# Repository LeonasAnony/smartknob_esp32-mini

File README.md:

# SmartKnob

SmartKnob is an open-source input device with software-configurable endstops and virtual detents. Original by [Scott Bezek](https://github.com/scottbez1/smartknob).

A brushless gimbal motor is paired with a magnetic encoder to provide closed-loop torque feedback control, making it
possible to dynamically create and adjust the feel of detents and endstops.

# Modifications
- ESP32-S3-MINI-1N8
- 24x WS2812 20x20 LED
- SMD Resistor 4 direction Force Sensor
- Accelerometer

# Handheld Version
Handheld Mod in branch [handheld](https://github.com/LeonasAnony/smartknob_esp32-mini/tree/handheld)

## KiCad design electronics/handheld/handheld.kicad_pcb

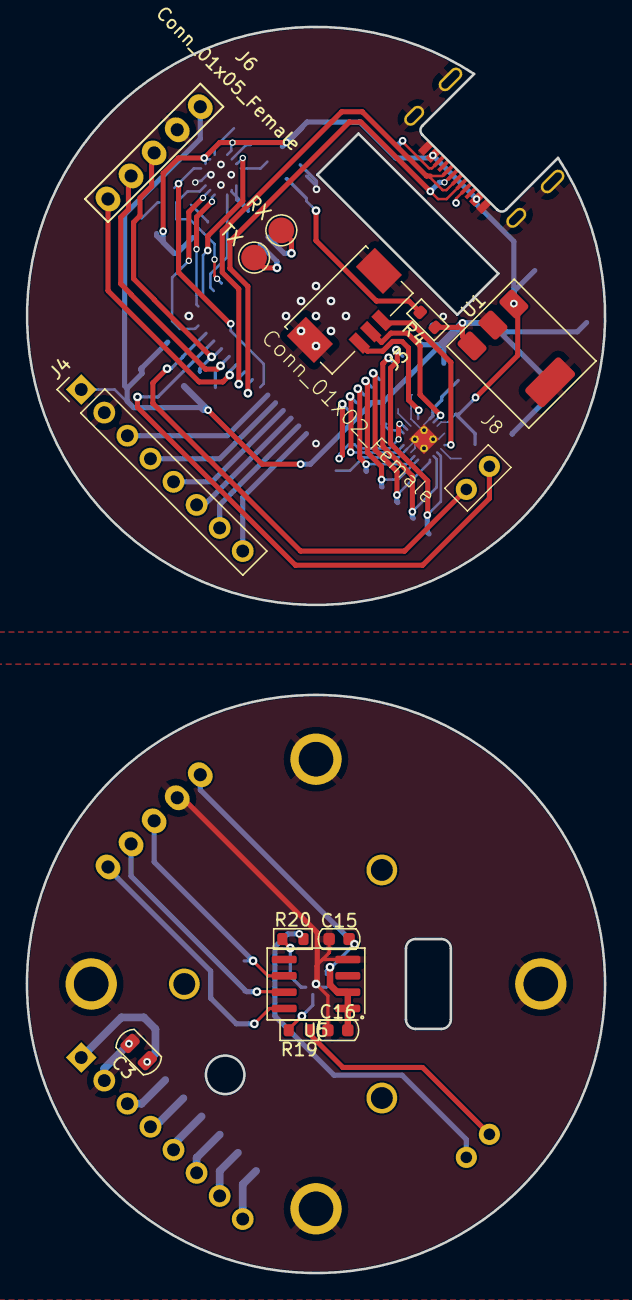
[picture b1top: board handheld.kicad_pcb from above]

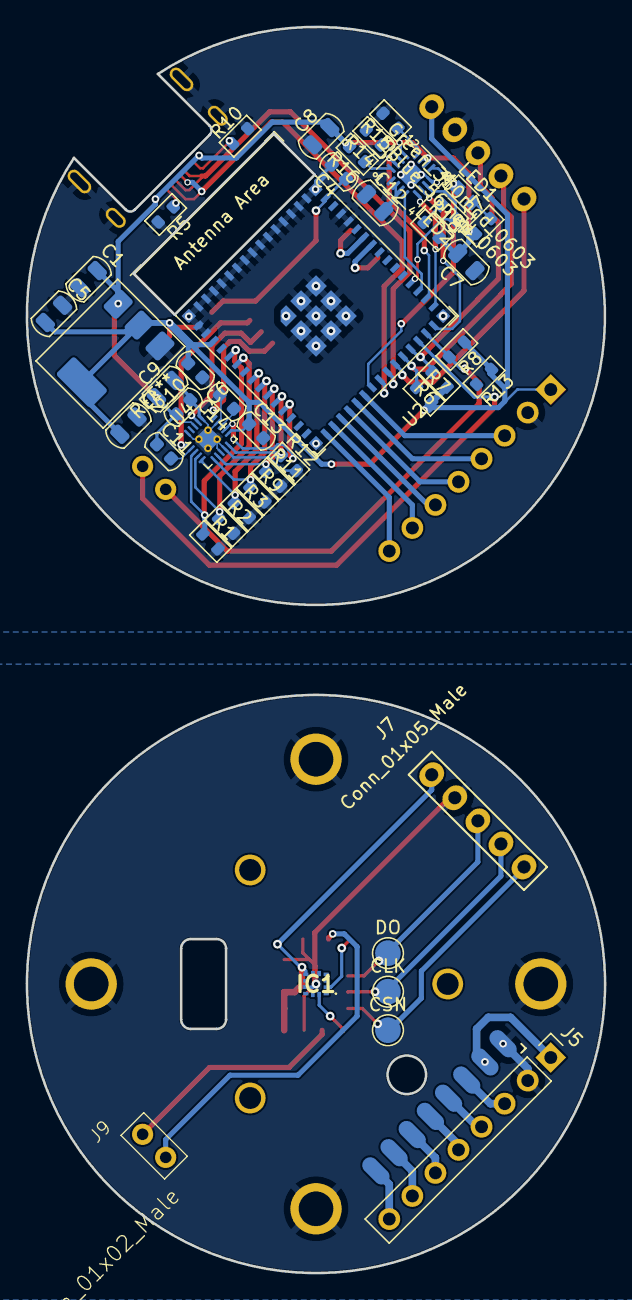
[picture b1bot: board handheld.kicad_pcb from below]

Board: 2 copper layers, 45.0 x 97.0 mm, 66 parts (43 on the bottom side), 60 nets.

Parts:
C1, C2, C3, C5: 10uF; C_0805_2012Metric
C4, C15: 1uF; C_0603_1608Metric
C6, C10, C11, C13, C14, C16: 0.1uF; C_0603_1608Metric
C7: 1uF; C_0805_2012Metric
C8, C12: 4.7uF; C_0805_2012Metric
C9: 22uF; C_0805_2012Metric
H1, H2, H3: MotorHole; MountingHole_M1.6
H4, H5, H6, H7: MountHole; MountingHole_2.7mm_M2.5_Pad
IC1: MXC6655XA
J1: LCD; SolderPads_2mm_8
J2: USB_C_Receptacle_USB2.0; USB4510_NoPaste
J3: BLDC; 532610371
J4: Conn_01x08_Female; Pins_1x08_2.54mm_TH
J5: Conn_01x08_Male; Pins_1x08_2.54mm_TH
J6: Conn_01x05_Female; Pins_1x05_2.54mm_TH
J7: Conn_01x05_Male; Pins_1x05_2.54mm_TH
J8: Conn_01x02_Female; Pins_1x02_2.54mm_TH
J9: Conn_01x02_Male; Pins_1x02_2.54mm_TH
LED1: Blue_56mcd_0603; LED_0603_1608Metric
LED2: Green_350mcd_0603; LED_0603_1608Metric
R1, R2, R3, R4, R9, R11, R12: 10k; R_0603_1608Metric
R5, R10: 5.1k; R_0603_1608Metric
R6, R7, R8, R13: 2.2k; R_0603_1608Metric
R14: 15k; R_0603_1608Metric
R15: 1.18k; R_0603_1608Metric
R16: 1.13k; R_0603_1608Metric
R17, R18: 1.5k; R_0603_1608Metric
R19, R20: 2.7k; R_0603_1608Metric
TP3: TX; TestPoint_Pad_D2.0mm_ValueSilk
TP4: RX; TestPoint_Pad_D2.0mm_ValueSilk
TP11: CSN; TestPoint_Pad_D2.0mm_ValueSilk
TP12: CLK; TestPoint_Pad_D2.0mm_ValueSilk
TP13: DO; TestPoint_Pad_D2.0mm_ValueSilk
U1: AP2114HA-3.3; SOT-223-3_TabPin2
U2: ESP32-S3-MINI-1
U3: BQ24072RGT; VQFN-16-1EP_3x3mm_P0.5mm_EP1.6x1.6mm
U4: TMC6300; QFN-20-1EP_3x3mm_P0.4mm_EP1.65x1.65mm_ThermalVias_LargerVia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
U5: MT6701-CT; SOIC-8_3.9x4.9mm_P1.27mm
Z6: dummy_keepouts; ViewKeepouts3d

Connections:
+3V3: C2.1, C5.1, C6.1, C13.1, J4.1, J6.1, R4.1, R6.1, R7.2, R8.1, R13.1, U1.3 (VO), U2.3 (3V3), U4.11 (VIO/~STDBY)
+5V: C1.1, C7.2, C8.2, C9.1, C10.1, C11.1, J2.A4 (VBUS), J2.A9 (VBUS), J2.B4 (VBUS), J2.B9 (VBUS), R16.2, R17.1, R18.2, U1.1 (VI), U3.10 (OUT), U3.11 (OUT), U3.13 (IN), U4.18 (VS)
/BAT: C12.2, U3.2 (BAT), U3.3 (BAT)
/CE: U2.33 (SPIDQS/GPIO37/FSPIQ/SUBSPIQ), U3.4 (~CE)
/CHG: LED1.1 (C), U2.22 (GPIO18/U1RXD/ADC2_CH7/CLK_OUT3), U3.9 (~CHG)
/EN1: U2.30 (GPIO48/SPICLK_N/SUBSPICLK_N_DIFF), U3.6 (EN1)
/EN2: U2.31 (SPIIO6/GPIO35/FSPID/SUBSPID), U3.5 (EN2)
/ESP32_EN: C4.1, R4.2, U2.45 (EN)
/PGOOD: LED2.1 (C), U2.34 (GPIO38/FSPIWP/SUBSPIWP), U3.7 (~PGOOD)
/TD: U2.32 (SPIIO7/GPIO36/FSPICLK/SUBSPICLK), U3.15 (TD)
/TMC_DIAG: U2.12 (GPIO8/TOUCH8/ADC1_CH7/SUBSPICS1), U4.12 (DIAG)
/TMC_UH: R1.1, U2.5 (GPIO1/TOUCH1/ADC1_CH0), U4.3 (UH)
/TMC_UL: R9.1, U2.9 (GPIO5/TOUCH5/ADC1_CH4), U4.6 (UL)
/TMC_VH: R2.1, U2.6 (GPIO2/TOUCH2/ADC1_CH1), U4.4 (VH)
/TMC_VL: R12.1, U2.11 (GPIO7/TOUCH7/ADC1_CH6), U4.10 (VL)
/TMC_WH: R3.1, U2.8 (GPIO4/TOUCH4/ADC1_CH3), U4.5 (WH)
/TMC_WL: R11.1, U2.10 (GPIO6/TOUCH6/ADC1_CH5), U4.7 (WL)
/USB_CC1: J2.A5 (CC1), R5.1
/USB_CC2: J2.B5 (CC2), R10.1
/USB_D+: J2.A6 (D+), J2.B6 (D+), U2.24 (GPIO20/U1CTS/ADC2_CH9/CLK_OUT1/USB_D+)
/USB_D-: J2.A7 (D-), J2.B7 (D-), U2.23 (GPIO19/U1RTS/ADC2_CH8/CLK_OUT2/USB_D-)
GND: C1.2, C2.2, C3.2, C4.2, C5.2, C6.2, C7.1, C8.1, C9.2, C10.2, C12.1, C13.2, C14.2, C15.1, C16.1, H4.1, H5.1, H6.1, H7.1, IC1.9 (GND), J1.1, J2.A1 (GND), J2.A12 (GND), J2.B1 (GND), J2.B12 (GND), J2.S1 (SHIELD), J4.2, J5.2, J6.2, J7.2, R1.2, R2.2, R3.2, R5.2, R9.2, R10.2, R11.2, R12.2, R14.2, R15.2, U1.2 (GND), U2.1 (GND), U2.2 (GND), U2.42 (GND), U2.43 (GND), U2.46 (GND), U3.8 (VSS), U3.17 (VSS), U4.8 (GND), U4.9 (GND), U4.14 (GND), U4.16 (BRUV), U4.20 (BRW), U4.PAD, U5.4 (GND)
unnamed: C3.1, J1.2, J5.1
unnamed: C11.2, U4.2 (VCP)
unnamed: C14.1, U4.13 (1V8OUT)
unnamed: C15.2, C16.2, IC1.7 (VDD), J7.1, U5.1 (VDD), U5.2 (MODE)
unnamed: IC1.2 (SDA), R20.1
unnamed: IC1.12 (SCL), R19.2
unnamed: J1.3, J5.3
unnamed: J1.4, J5.4
unnamed: J1.5, J5.5
unnamed: J1.6, J5.6
unnamed: J1.7, J5.7
unnamed: J1.8, J5.8
unnamed: J3.1, U4.1 (W)
unnamed: J3.2, U4.17 (V)
unnamed: J3.3, U4.15 (U)
unnamed: J4.3, U2.21 (GPIO17/U1TXD/ADC2_CH6)
unnamed: J4.4, U2.20 (GPIO16/U0CTS/ADC2_CH5/XTAL_32K_NH5)
unnamed: J4.5, U2.19 (GPIO15/U0RTS/ADC2_CH4/XTAL_32K_P)
unnamed: J4.6, U2.18 (GPIO14/TOUCH14/ADC2_CH3/FSPIWP/FSPIDQS/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)
unnamed: J4.7, U2.17 (GPIO13/TOUCH13/ADC2_CH2/FSPIQ/FSPIIO7/S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)
unnamed: J4.8, U2.16 (GPIO12/TOUCH11/ADC2_CH0/FSPICS0/FSPIIO4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)
unnamed: J6.3, U2.27 (GPIO47/SPICLK_P/SUBSPICLK_P_DIFF)
unnamed: J6.4, U2.26 (GPIO26)
unnamed: J6.5, U2.25 (GPIO21)
unnamed: J7.3, TP13.1, U5.6 (A/U/SDA/DO)
unnamed: J7.4, TP12.1, U5.7 (B/V/SCL/CLK)
unnamed: J7.5, TP11.1, U5.8 (Z/W/CSN)
unnamed: J8.1, U2.28 (SPIIO4/GPIO33/FSPIHD/SUBSPIHD)
unnamed: J8.2, U2.29 (SPIIO5/GPIO34/FSPICS0/SUBSPICS0)
unnamed: J9.1, R19.1
unnamed: J9.2, R20.2
unnamed: LED1.2 (A), R17.2
unnamed: LED2.2 (A), R18.1
unnamed: R14.1, U3.14 (TMR)
unnamed: R15.1, U3.12 (ILIM)
unnamed: R16.1, U3.16 (ISET)
unnamed: TP3.1, U2.39 (U0TXD/GPIO43/CLK_OUT1)
unnamed: TP4.1, U2.40 (U0RXD/GPIO44/CLK_OUT2)

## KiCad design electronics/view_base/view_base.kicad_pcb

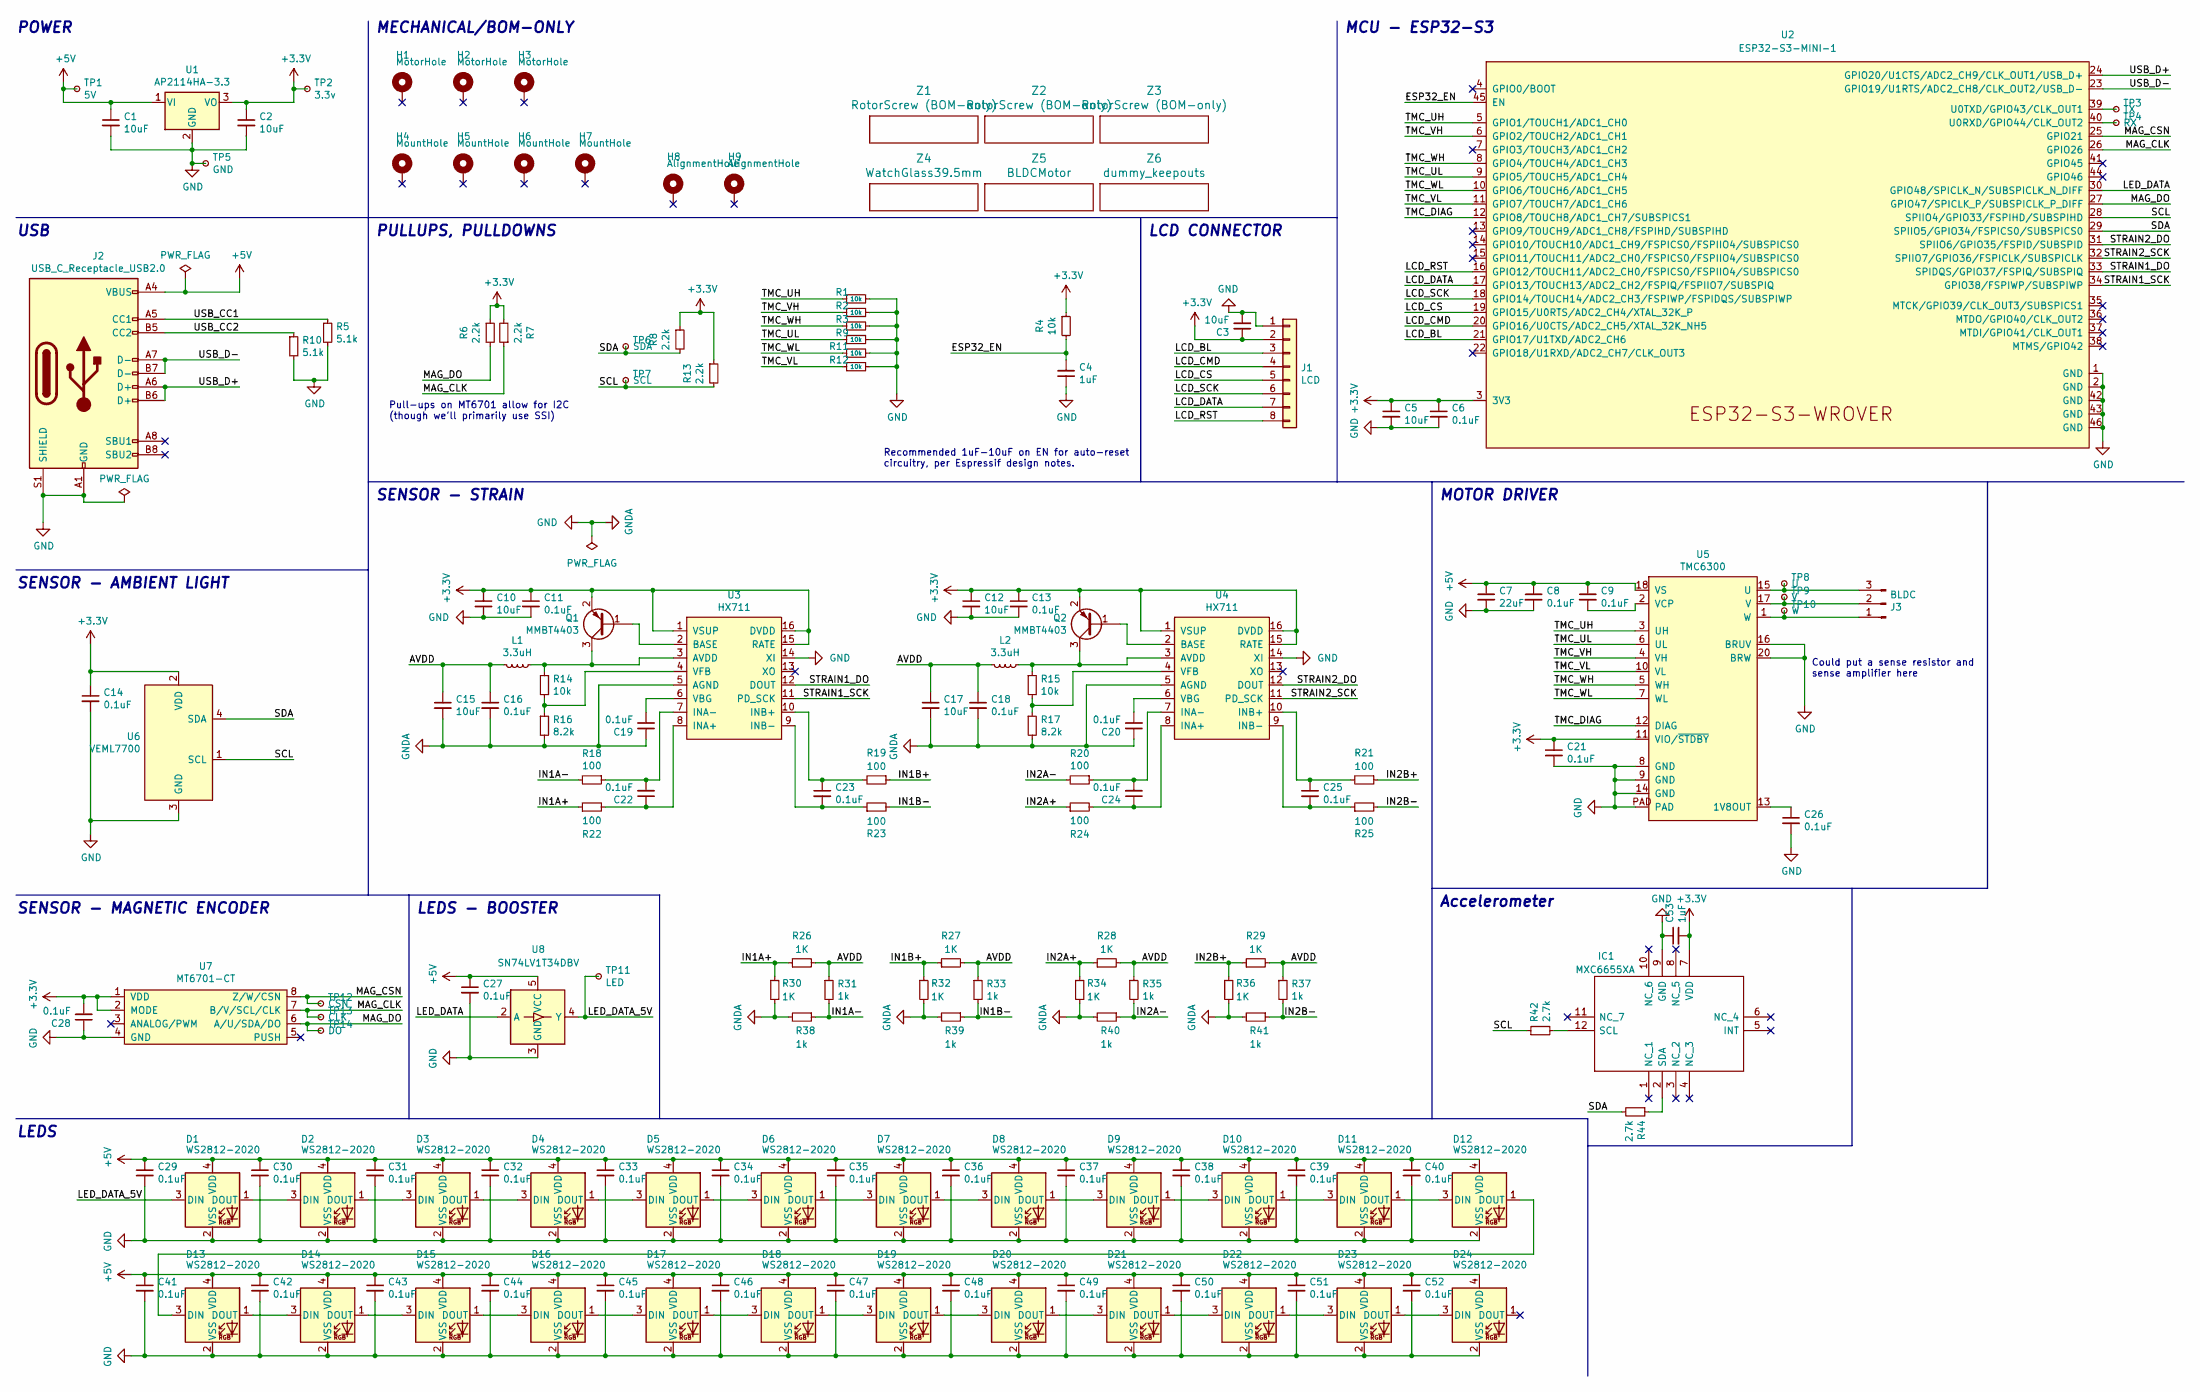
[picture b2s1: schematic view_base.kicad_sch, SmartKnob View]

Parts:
C1, C2, C3, C5, C10, C12, C15, C17: 10uF; C_0805_2012Metric; LCSC C2922480
C4: 1uF; C_0603_1608Metric; Mouser 187-CL10A105KA8NNNC
C6, C8, C9, C11, C13, C14, C16, C18, C19, C20, C21, C22, C23, C24, C25, C26, C27, C28, C29, C30, C31, C32, C33, C34, C35, C36, C37, C38, C39, C40, C41, C42, C43, C44, C45, C46, C47, C48, C49, C50, C51, C52: 0.1uF; C_0603_1608Metric; LCSC C1591
C7: 22uF; C_0805_2012Metric; LCSC C98190
C53: 1uF; C_0603_1608Metric; LCSC C1591
D1, D2, D3, D4, D5, D6, D7, D8, D9, D10, D11, D12, D13, D14, D15, D16, D17, D18, D19, D20, D21, D22, D23, D24: WS2812-2020; Digikey 1528-4691-ND
H1, H2, H3: MotorHole; MountingHole_M1.6
H4, H5, H6, H7: MountHole; MountingHole_2.2mm_M2_ISO7380_Pad_NonVirtual
H8, H9: AlignmentHole; MountingHole_2.2mm_M2_ISO7380_Pad_NonVirtual
IC1: MXC6655XA; Mouser Part Number 438-MXC6655XA
J1: LCD; SolderPads_2mm_8
J2: USB_C_Receptacle_USB2.0; USB4510_NoPaste; LCSC C428463
J3: BLDC; 532610371; LCSC C293630
L1, L2: 3.3uH; L_0805_2012Metric; LCSC C307744
Q1, Q2: MMBT4403; SOT-23; LCSC C78864
R1, R2, R3, R4, R9, R11, R12, R14, R15: 10k; R_0603_1608Metric; LCSC C98220
R5, R10: 5.1k; R_0603_1608Metric; LCSC C105580
R6, R7, R8, R13: 2.2k; R_0603_1608Metric; LCSC C4190
R16, R17: 8.2k; R_0603_1608Metric; LCSC C114637
R18, R19, R20, R21, R22, R23, R24, R25: 100; R_0603_1608Metric; LCSC C319953
R26, R27, R28, R29, R30, R32, R34, R36: 1K; R_2512_6332Metric
R31, R33, R35, R37, R38, R39, R40, R41: 1k; R_0603_1608Metric; LCSC C98220
R42, R44: 2.7k; R_0603_1608Metric; LCSC C98220
TP1: 5V; TestPoint_Pad_D2.0mm_ValueSilk
TP2: 3.3v; TestPoint_Pad_D2.0mm_ValueSilk
TP3: TX; TestPoint_Pad_D2.0mm_ValueSilk
TP4: RX; TestPoint_Pad_D2.0mm_ValueSilk
TP5: GND; TestPoint_Pad_D2.0mm_ValueSilk
TP6: SDA; TestPoint_Pad_D2.0mm_ValueSilk
TP7: SCL; TestPoint_Pad_D2.0mm_ValueSilk
TP8: U; TestPoint_Pad_D2.0mm_ValueSilk
TP9: V; TestPoint_Pad_D2.0mm_ValueSilk
TP10: W; TestPoint_Pad_D2.0mm_ValueSilk
TP11: LED; TestPoint_Pad_D2.0mm_ValueSilk
TP12: CSN; TestPoint_Pad_D2.0mm_ValueSilk
TP13: CLK; TestPoint_Pad_D2.0mm_ValueSilk
TP14: DO; TestPoint_Pad_D2.0mm_ValueSilk
U1: AP2114HA-3.3; SOT-223-3_TabPin2; LCSC C460314
U2: ESP32-S3-MINI-1
U3, U4: HX711; SOIC-16_3.9x9.9mm_P1.27mm; LCSC C43656
U5: TMC6300; QFN-20-1EP_3x3mm_P0.4mm_EP1.65x1.65mm_ThermalVias_LargerVia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; Digikey TMC6300-LA-T
U6: VEML7700; VEML7700-TOP; Digikey VEML7700-TT
U7: MT6701-CT; SOIC-8_3.9x4.9mm_P1.27mm; LCSC C2856764
U8: SN74LV1T34DBV; SOT-23-5; LCSC C100024
Z1, Z2, Z3: RotorScrew (BOM-only); bom_only_no_pin
Z4: WatchGlass39.5mm; bom_only_no_pin
Z5: BLDCMotor; bom_only_no_pin
Z6: dummy_keepouts; ViewKeepouts3d

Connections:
+3V3: C2.1, C3.1, C5.1, C6.1, C10.1, C11.1, C12.1, C13.1, C14.1, C21.1, C28.2, C53.2, IC1.7 (VDD), J1.2, Q1.2 (E), Q2.2 (E), R4.1, R6.1, R7.2, R8.1, R13.1, TP2.1, U1.3 (VO), U2.3 (3V3), U3.1 (VSUP), U3.15 (RATE), U3.16 (DVDD), U4.1 (VSUP), U4.15 (RATE), U4.16 (DVDD), U5.11 (VIO/~STDBY), U6.2 (VDD), U7.1 (VDD), U7.2 (MODE)
+5V: C1.1, C7.1, C8.1, C9.1, C27.1, C29.1, C30.1, C31.1, C32.1, C33.1, C34.1, C35.1, C36.1, C37.1, C38.1, C39.1, C40.1, C41.1, C42.1, C43.1, C44.1, C45.1, C46.1, C47.1, C48.1, C49.1, C50.1, C51.1, C52.1, D1.4 (VDD), D2.4 (VDD), D3.4 (VDD), D4.4 (VDD), D5.4 (VDD), D6.4 (VDD), D7.4 (VDD), D8.4 (VDD), D9.4 (VDD), D10.4 (VDD), D11.4 (VDD), D12.4 (VDD), D13.4 (VDD), D14.4 (VDD), D15.4 (VDD), D16.4 (VDD), D17.4 (VDD), D18.4 (VDD), D19.4 (VDD), D20.4 (VDD), D21.4 (VDD), D22.4 (VDD), D23.4 (VDD), D24.4 (VDD), J2.A4 (VBUS), J2.A9 (VBUS), J2.B4 (VBUS), J2.B9 (VBUS), TP1.1, U1.1 (VI), U5.18 (VS), U8.5 (VCC)
/ESP32_EN: C4.1, R4.2, U2.45 (EN)
/IN1A+: R22.1, R26.1, R30.1
/IN1A-: R18.2, R31.2, R38.1
/IN1B+: R19.1, R27.1, R32.1
/IN1B-: R23.2, R33.2, R39.1
/IN2A+: R24.1, R28.1, R34.1
/IN2A-: R20.2, R35.2, R40.1
/IN2B+: R21.1, R29.1, R36.1
/LCD_BL: J1.3, U2.21 (GPIO17/U1TXD/ADC2_CH6)
/LCD_CMD: J1.4, U2.20 (GPIO16/U0CTS/ADC2_CH5/XTAL_32K_NH5)
/LCD_CS: J1.5, U2.19 (GPIO15/U0RTS/ADC2_CH4/XTAL_32K_P)
/LCD_DATA: J1.7, U2.17 (GPIO13/TOUCH13/ADC2_CH2/FSPIQ/FSPIIO7/S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)
/LCD_RST: J1.8, U2.16 (GPIO12/TOUCH11/ADC2_CH0/FSPICS0/FSPIIO4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)
/LCD_SCK: J1.6, U2.18 (GPIO14/TOUCH14/ADC2_CH3/FSPIWP/FSPIDQS/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)
/LED_DATA: U2.30 (GPIO48/SPICLK_N/SUBSPICLK_N_DIFF), U8.2 (A)
/LED_DATA_5V: D1.3 (DIN), TP11.1, U8.4 (Y)
/MAG_CLK: R7.1, TP13.1, U2.26 (GPIO26), U7.7 (B/V/SCL/CLK)
/MAG_CSN: TP12.1, U2.25 (GPIO21), U7.8 (Z/W/CSN)
/MAG_DO: R6.2, TP14.1, U2.27 (GPIO47/SPICLK_P/SUBSPICLK_P_DIFF), U7.6 (A/U/SDA/DO)
/SCL: R13.2, R42.1, TP7.1, U2.28 (SPIIO4/GPIO33/FSPIHD/SUBSPIHD), U6.1 (SCL)
/SDA: R8.2, R44.2, TP6.1, U2.29 (SPIIO5/GPIO34/FSPICS0/SUBSPICS0), U6.4 (SDA)
/STRAIN1_DO: U2.33 (SPIDQS/GPIO37/FSPIQ/SUBSPIQ), U3.12 (DOUT)
/STRAIN1_SCK: U2.34 (GPIO38/FSPIWP/SUBSPIWP), U3.11 (PD_SCK)
/STRAIN2_DO: U2.31 (SPIIO6/GPIO35/FSPID/SUBSPID), U4.12 (DOUT)
/STRAIN2_SCK: U2.32 (SPIIO7/GPIO36/FSPICLK/SUBSPICLK), U4.11 (PD_SCK)
/TMC_DIAG: U2.12 (GPIO8/TOUCH8/ADC1_CH7/SUBSPICS1), U5.12 (DIAG)
/TMC_UH: R1.1, U2.5 (GPIO1/TOUCH1/ADC1_CH0), U5.3 (UH)
/TMC_UL: R9.1, U2.9 (GPIO5/TOUCH5/ADC1_CH4), U5.6 (UL)
/TMC_VH: R2.1, U2.6 (GPIO2/TOUCH2/ADC1_CH1), U5.4 (VH)
/TMC_VL: R12.1, U2.11 (GPIO7/TOUCH7/ADC1_CH6), U5.10 (VL)
/TMC_WH: R3.1, U2.8 (GPIO4/TOUCH4/ADC1_CH3), U5.5 (WH)
/TMC_WL: R11.1, U2.10 (GPIO6/TOUCH6/ADC1_CH5), U5.7 (WL)
/USB_CC1: J2.A5 (CC1), R5.1
/USB_CC2: J2.B5 (CC2), R10.1
/USB_D+: J2.A6 (D+), J2.B6 (D+), U2.24 (GPIO20/U1CTS/ADC2_CH9/CLK_OUT1/USB_D+)
/USB_D-: J2.A7 (D-), J2.B7 (D-), U2.23 (GPIO19/U1RTS/ADC2_CH8/CLK_OUT2/USB_D-)
GND: C1.2, C2.2, C3.2, C4.2, C5.2, C6.2, C7.2, C8.2, C10.2, C11.2, C12.2, C13.2, C14.2, C15.2, C16.2, C17.2, C18.2, C19.1, C20.1, C21.2, C26.2, C27.2, C28.1, C29.2, C30.2, C31.2, C32.2, C33.2, C34.2, C35.2, C36.2, C37.2, C38.2, C39.2, C40.2, C41.2, C42.2, C43.2, C44.2, C45.2, C46.2, C47.2, C48.2, C49.2, C50.2, C51.2, C52.2, C53.1, D1.2 (VSS), D2.2 (VSS), D3.2 (VSS), D4.2 (VSS), D5.2 (VSS), D6.2 (VSS), D7.2 (VSS), D8.2 (VSS), D9.2 (VSS), D10.2 (VSS), D11.2 (VSS), D12.2 (VSS), D13.2 (VSS), D14.2 (VSS), D15.2 (VSS), D16.2 (VSS), D17.2 (VSS), D18.2 (VSS), D19.2 (VSS), D20.2 (VSS), D21.2 (VSS), D22.2 (VSS), D23.2 (VSS), D24.2 (VSS), IC1.9 (GND), J1.1, J2.A1 (GND), J2.A12 (GND), J2.B1 (GND), J2.B12 (GND), J2.S1 (SHIELD), R1.2, R2.2, R3.2, R5.2, R9.2, R10.2, R11.2, R12.2, R16.2, R17.2, R30.2, R32.2, R34.2, R36.2, R38.2, R39.2, R40.2, R41.2, TP5.1, U1.2 (GND), U2.1 (GND), U2.2 (GND), U2.42 (GND), U2.43 (GND), U2.46 (GND), U3.5 (AGND), U3.14 (XI), U4.5 (AGND), U4.14 (XI), U5.8 (GND), U5.9 (GND), U5.14 (GND), U5.16 (BRUV), U5.20 (BRW), U5.PAD, U6.3 (GND), U7.4 (GND), U8.3 (GND)
unnamed: C9.2, U5.2 (VCP)
unnamed: C19.2, U3.6 (VBG)
unnamed: C20.2, U4.6 (VBG)
unnamed: C22.1, R22.2, U3.8 (INA+)
unnamed: C22.2, R18.1, U3.7 (INA-)
unnamed: C23.1, R19.2, U3.10 (INB+)
unnamed: C23.2, R23.1, U3.9 (INB-)
unnamed: C24.1, R24.2, U4.8 (INA+)
unnamed: C24.2, R20.1, U4.7 (INA-)
unnamed: C25.1, R21.2, U4.10 (INB+)
unnamed: C25.2, R25.1, U4.9 (INB-)
unnamed: C26.1, U5.13 (1V8OUT)
unnamed: D1.1 (DOUT), D2.3 (DIN)
unnamed: D2.1 (DOUT), D3.3 (DIN)
unnamed: D3.1 (DOUT), D4.3 (DIN)
unnamed: D4.1 (DOUT), D5.3 (DIN)
unnamed: D5.1 (DOUT), D6.3 (DIN)
unnamed: D6.1 (DOUT), D7.3 (DIN)
unnamed: D7.1 (DOUT), D8.3 (DIN)
unnamed: D8.1 (DOUT), D9.3 (DIN)
unnamed: D10.1 (DOUT), D11.3 (DIN)
unnamed: D9.1 (DOUT), D10.3 (DIN)
unnamed: D11.1 (DOUT), D12.3 (DIN)
unnamed: D12.1 (DOUT), D13.3 (DIN)
unnamed: D13.1 (DOUT), D14.3 (DIN)
unnamed: D14.1 (DOUT), D15.3 (DIN)
unnamed: D15.1 (DOUT), D16.3 (DIN)
unnamed: D16.1 (DOUT), D17.3 (DIN)
unnamed: D17.1 (DOUT), D18.3 (DIN)
unnamed: D18.1 (DOUT), D19.3 (DIN)
unnamed: D19.1 (DOUT), D20.3 (DIN)
unnamed: D20.1 (DOUT), D21.3 (DIN)
unnamed: D21.1 (DOUT), D22.3 (DIN)
unnamed: D22.1 (DOUT), D23.3 (DIN)
unnamed: D23.1 (DOUT), D24.3 (DIN)
unnamed: IC1.2 (SDA), R44.1
unnamed: IC1.12 (SCL), R42.2
unnamed: J3.1, TP10.1, U5.1 (W)
unnamed: J3.2, TP9.1, U5.17 (V)
unnamed: J3.3, TP8.1, U5.15 (U)
unnamed: L1.1, Q1.3 (C), R14.1, U3.3 (AVDD)
unnamed: L2.1, Q2.3 (C), R15.1, U4.3 (AVDD)
unnamed: Q1.1 (B), U3.2 (BASE)
unnamed: Q2.1 (B), U4.2 (BASE)
unnamed: R14.2, R16.1, U3.4 (VFB)
unnamed: R15.2, R17.1, U4.4 (VFB)
unnamed: TP3.1, U2.39 (U0TXD/GPIO43/CLK_OUT1)
unnamed: TP4.1, U2.40 (U0RXD/GPIO44/CLK_OUT2)

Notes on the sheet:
SENSOR - STRAIN
MECHANICAL/BOM-ONLY
Accelerometer
MCU - ESP32-S3
LEDS
PULLUPS, PULLDOWNS
Could put a sense resistor and sense amplifier here
MOTOR DRIVER
Recommended 1uF-10uF on EN for auto-reset circuitry, per Espressif design notes.
POWER
SENSOR - AMBIENT LIGHT
LEDS - BOOSTER
SENSOR - MAGNETIC ENCODER
Pull-ups on MT6701 allow for I2C (though we'll primarily use SSI)
USB
LCD CONNECTOR

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
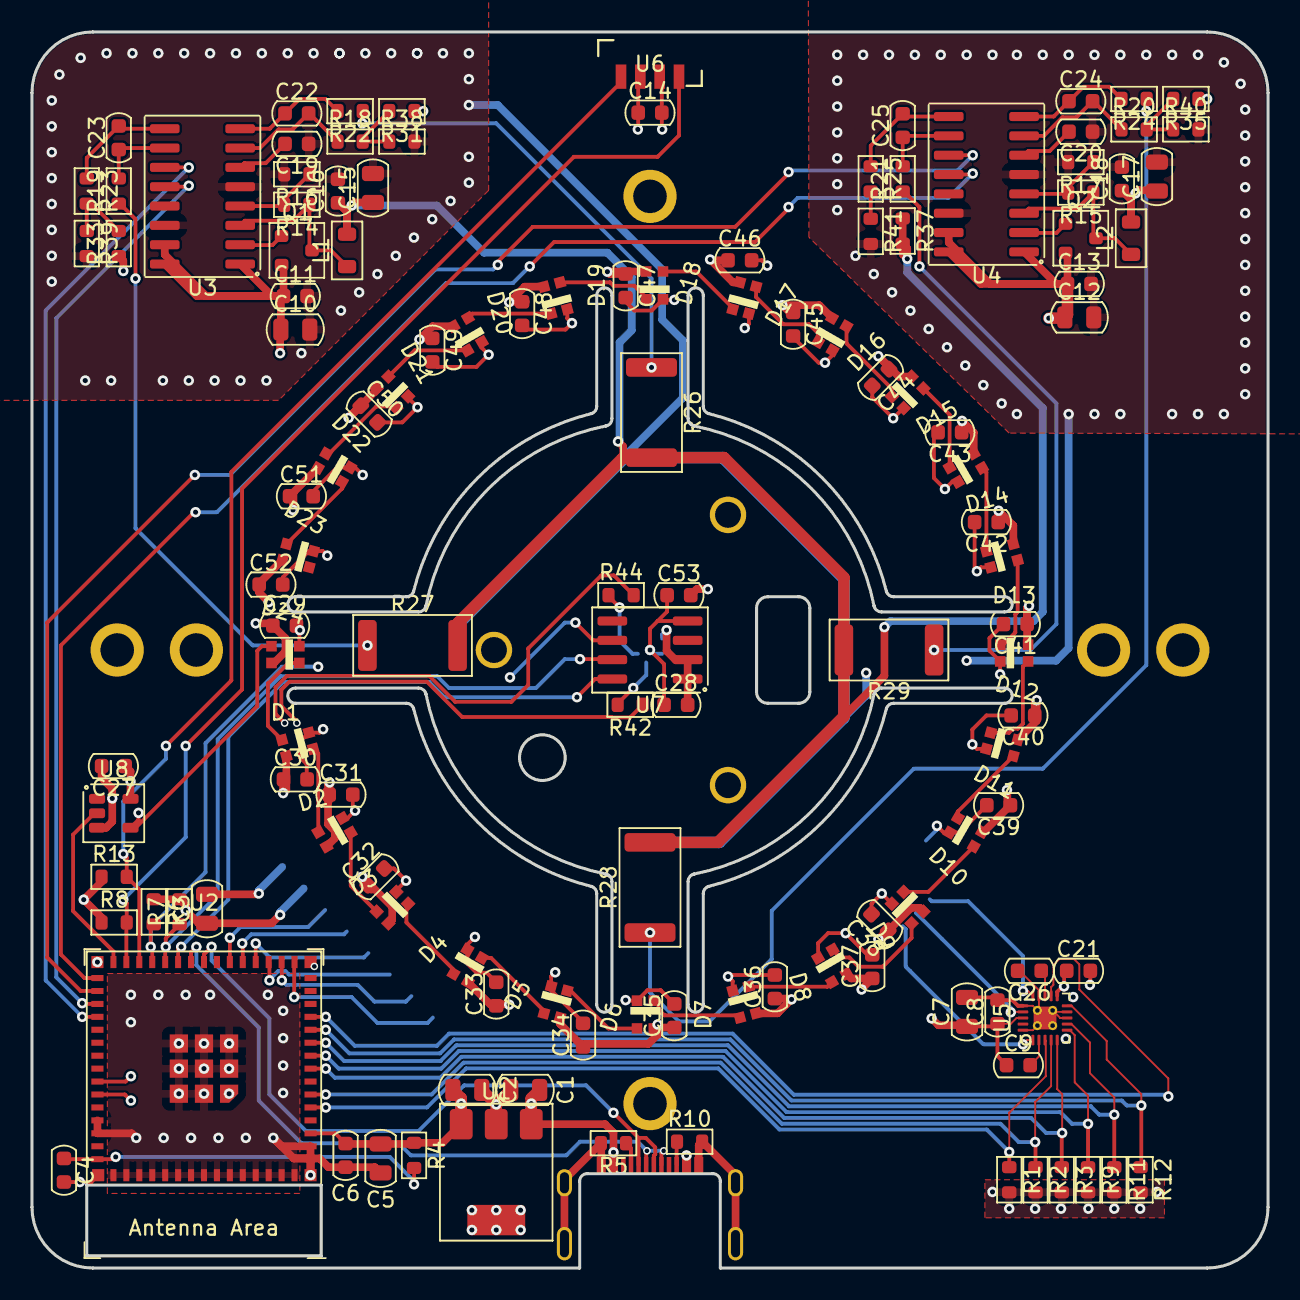
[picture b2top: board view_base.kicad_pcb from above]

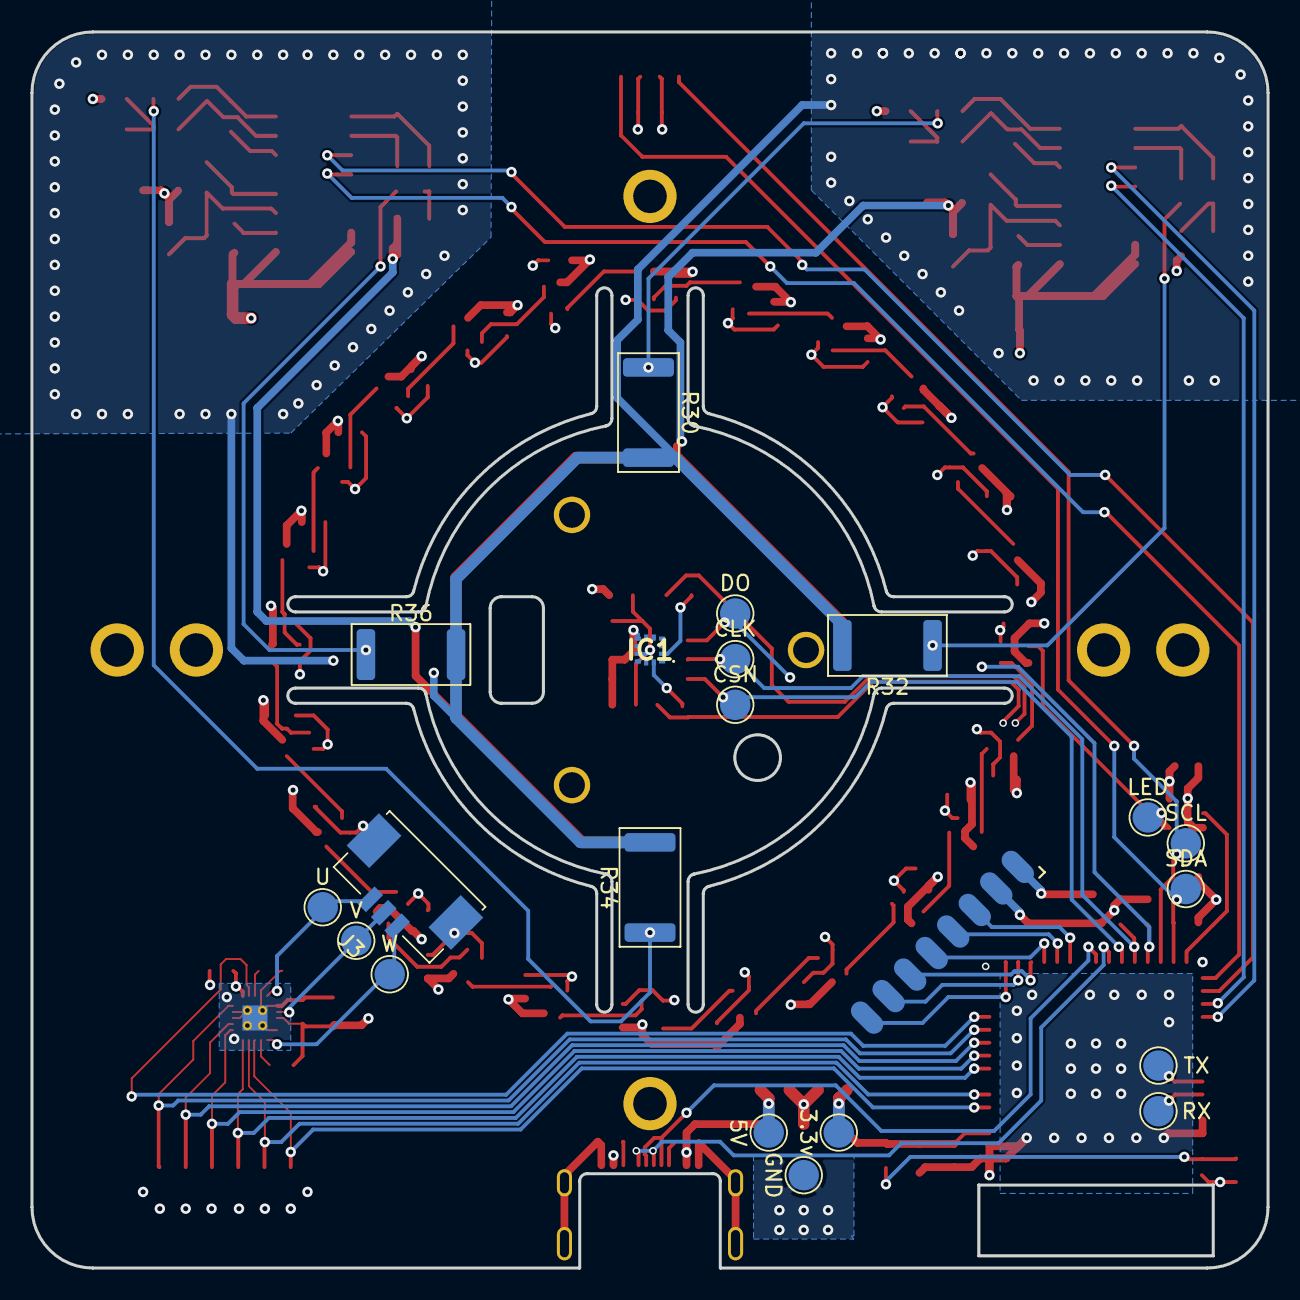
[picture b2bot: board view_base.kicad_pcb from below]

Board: 4 copper layers, 81.2 x 81.2 mm, 165 parts (21 on the bottom side), 89 nets.

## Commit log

2022-10-29 Mod v1
    - ESP32-S3-MINI-1N8
    - 24x WS2812 20x20 LED
    - SMD Resistors 4 direction Force Sensor
    - Accelerometer
2022-10-29 Handheld Init
    My own handheld idea. Prototyping stage. Lipo Batterys. Accelerometer.
2022-10-29 Gerbers for Release

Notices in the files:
parts and their libraries:
Copyright 2021 Accelerated Designs. All rights reserved.
